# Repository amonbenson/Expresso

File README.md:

# Expresso

An open source USB&ndash;Midi&ndash;Expression pedal converter.

⚠️ Please note: This project is currently under heavy development and not yet functional. ⚠️

✔️ Supports sustain pedals of any polarity<br>
✔️ Supports any kind of three-pin analog expression pedal<br>
✔️ Pedal state can be output to both Din- or USB-Midi<br>
✔️ Can be used as a classic USB-Din-Midi adapter<br>

... to be continued.

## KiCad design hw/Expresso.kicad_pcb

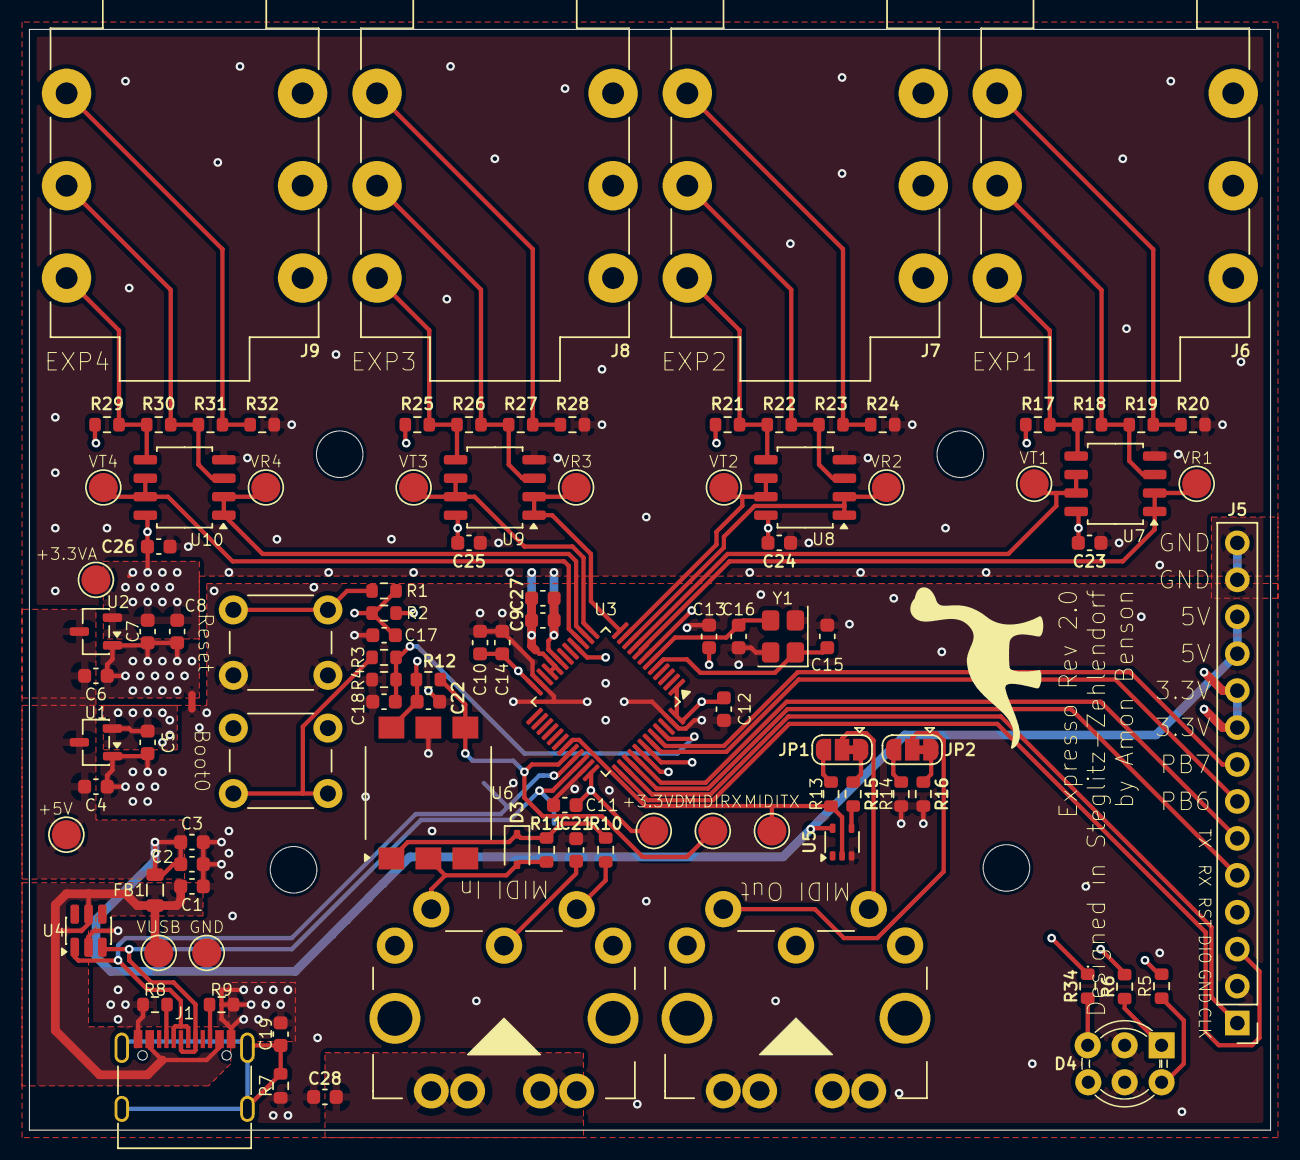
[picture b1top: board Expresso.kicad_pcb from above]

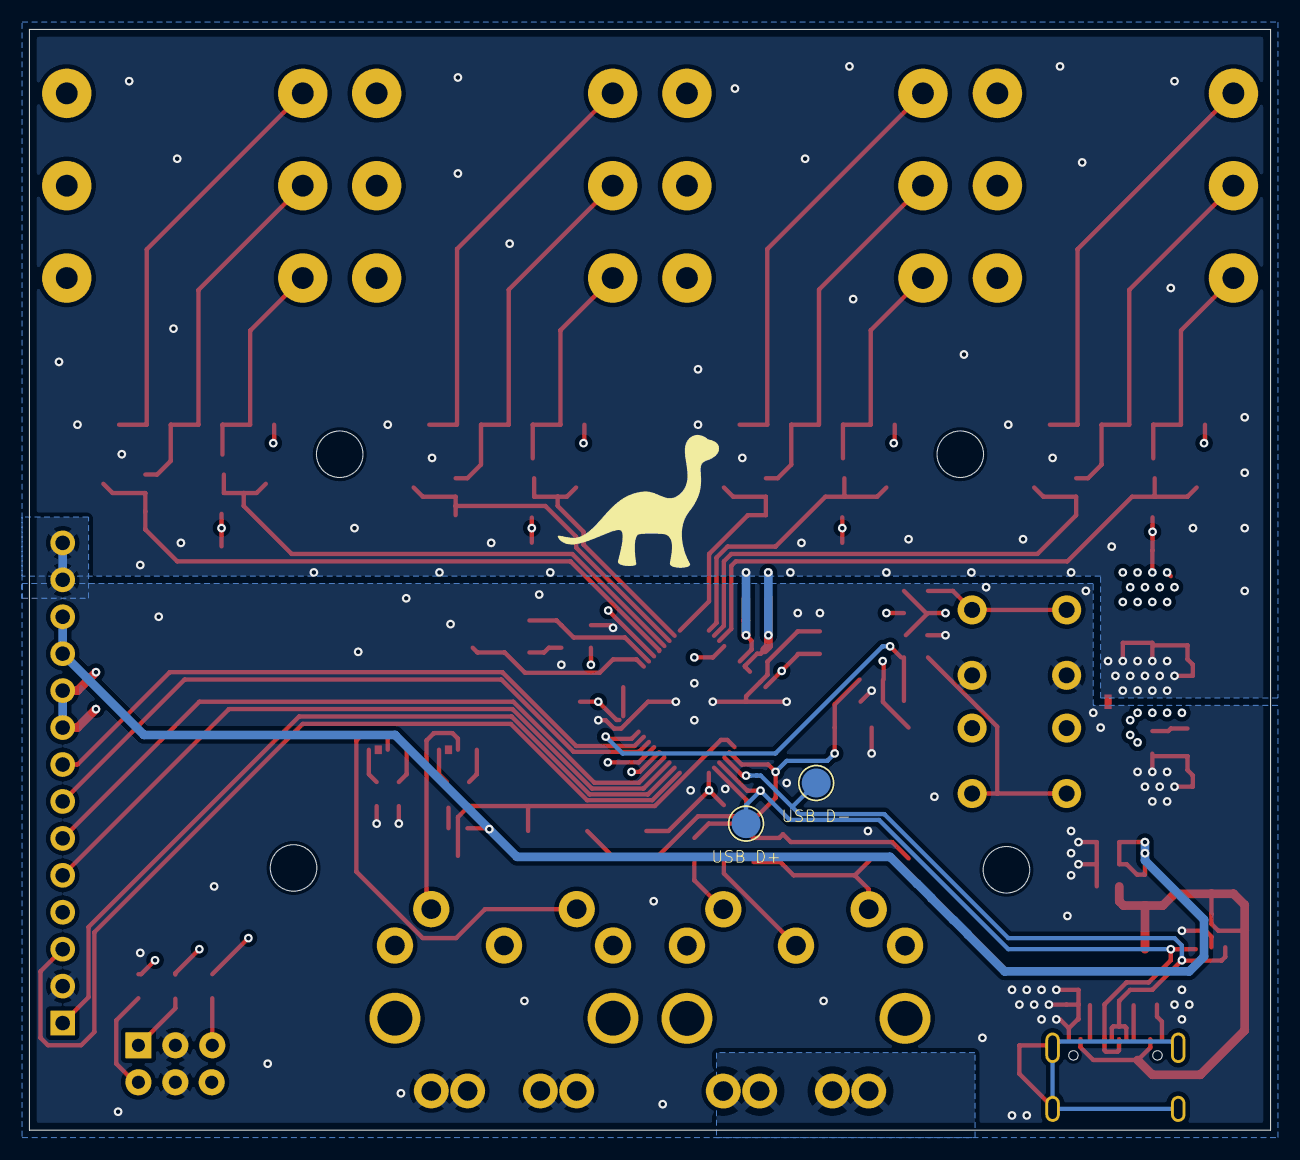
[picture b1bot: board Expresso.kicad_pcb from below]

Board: 4 copper layers, 85.3 x 75.7 mm, 108 parts (2 on the bottom side), 63 nets.

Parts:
C1: 10n; C_0603_1608Metric
C2, C8, C9, C11, C12, C13, C14, C17, C18, C21, C22, C23, C24, C25, C26, C28: 100n; C_0603_1608Metric
C3: 4.7u; C_0603_1608Metric
C4, C5, C6, C7, C27: 1u; C_0603_1608Metric
C10: 10u; C_0603_1608Metric
C15, C16: 12p; C_0603_1608Metric
C19: 4.7n; C_0603_1608Metric
D3: 1N4148WS; D_SOD-323
D4: LED_RBK_GBK; LED_D5.0mm_6Pin
FB1: 33Ω@100MHz; L_0805_2012Metric
H1, H2, H3, H4: MountingHole; MountingHole_3.2mm_M3
J1: USB_C_Receptacle_USB2.0_16P; USB_C_Receptacle_G-Switch_GT-USB-7010ASV
J2: Midi In; DIN5_MIDI_MultiGround
J3: Midi Out; DIN5_MIDI_MultiGround
J5: Debug; PinHeader_1x14_P2.54mm_Vertical
J6, J7, J8, J9: Exp; Jack_6.35mm_Neutrik_NMJ6HFD4_Horizontal
JP1: MidiOut_Src; SolderJumper-3_P1.3mm_Bridged12_RoundedPad1.0x1.5mm
JP2: MidiOut_Snk; SolderJumper-3_P1.3mm_Bridged12_RoundedPad1.0x1.5mm
NT1: GND_GNDA; NetTie-2_SMD_Pad0.5mm
R1, R3, R5, R11, R12: 1k; R_0603_1608Metric
R2, R4, R17, R20, R21, R24, R25, R28, R29, R32: 10k; R_0603_1608Metric
R6: 2.2k; R_0603_1608Metric
R7: 1M; R_0603_1608Metric
R8, R9: 5.1k; R_0603_1608Metric
R10, R15, R16: 220; R_0603_1608Metric
R13, R14: 47; R_0603_1608Metric
R18, R19, R22, R23, R26, R27, R30, R31: 100k; R_0603_1608Metric
R34: 680; R_0603_1608Metric
SW1: Reset; SW_PUSH_6mm
SW2: Boot0; SW_PUSH_6mm
TP1: VUSB; TestPoint_Pad_D2.0mm
TP2: +5V; TestPoint_Pad_D2.0mm
TP3: +3.3V; TestPoint_Pad_D2.0mm
TP4: +3.3VA; TestPoint_Pad_D2.0mm
TP5: GND; TestPoint_Pad_D2.0mm
TP6: USB D+; TestPoint_Pad_D2.0mm
TP7: USB D-; TestPoint_Pad_D2.0mm
TP8: MIDI_RX; TestPoint_Pad_D2.0mm
TP9: MIDI_TX; TestPoint_Pad_D2.0mm
TP10, TP12, TP14, TP16: VR; TestPoint_Pad_D2.0mm
TP11, TP13, TP15, TP17: VT; TestPoint_Pad_D2.0mm
U1, U2: XC6206P332MR; SOT-23-3
U3: STM32G431CBT6; LQFP-48_7x7mm_P0.5mm
U4: SRV05-4; SOT-23-6
U5: 74AHCT1G17GWH; SOT-353_SC-70-5
U6: H11L1; SOP-6_6.35x8.51mm_P02.54mm
U7, U8, U9, U10: NE5532; NE5532DR
Y1: 16 MHz; Crystal_SMD_3225-4Pin_3.2x2.5mm

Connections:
+3.3V: C5.1, C10.1, C11.1, C12.1, C13.1, C14.1, C22.1, J5.9, J5.10, R2.2, R12.1, SW2.2, TP3.1, U1.2 (VO), U3.1 (VBAT), U3.24 (VDD), U3.36 (VDD), U3.48 (VDD), U6.6
+3.3VA: C7.1, C8.1, C9.1, C23.1, C24.1, C25.1, C26.1, C27.1, R17.1, R21.1, R25.1, R29.1, TP4.1, U2.2 (VO), U3.20 (VREF+), U3.21 (VDDA), U7.8 (V+), U8.8 (V+), U9.8 (V+), U10.8 (V+)
+5V: C2.1, C3.1, C4.1, C6.1, FB1.2, J5.11, J5.12, TP2.1, U1.3 (VI), U2.3 (VI), U5.5 (VCC)
/Expression Inputs/Expression Input 1/EXP_R: J6.R, R18.2, R19.1, U7.3 (+)
/Expression Inputs/Expression Input 1/EXP_S: J6.S, R19.2, R20.1
/Expression Inputs/Expression Input 1/EXP_T: J6.T, R17.2, R18.1, U7.5 (+)
/Expression Inputs/Expression Input 2/EXP_R: J7.R, R22.2, R23.1, U8.3 (+)
/Expression Inputs/Expression Input 2/EXP_S: J7.S, R23.2, R24.1
/Expression Inputs/Expression Input 2/EXP_T: J7.T, R21.2, R22.1, U8.5 (+)
/Expression Inputs/Expression Input 3/EXP_R: J8.R, R26.2, R27.1, U9.3 (+)
/Expression Inputs/Expression Input 3/EXP_S: J8.S, R27.2, R28.1
/Expression Inputs/Expression Input 3/EXP_T: J8.T, R25.2, R26.1, U9.5 (+)
/Expression Inputs/Expression Input 4/EXP_R: J9.R, R30.2, R31.1, U10.3 (+)
/Expression Inputs/Expression Input 4/EXP_S: J9.S, R31.2, R32.1
/Expression Inputs/Expression Input 4/EXP_T: J9.T, R29.2, R30.1, U10.5 (+)
/Midi Connector/MIDI_IN_SHIELD: C28.1, J2.S
/USB Connector/USB_SHIELD: C19.1, J1.S1 (SHIELD), R7.1
GND: C1.2, C2.2, C3.2, C4.2, C5.2, C10.2, C11.2, C12.2, C13.2, C14.2, C15.2, C16.2, C17.2, C18.2, C19.2, C21.2, C22.2, C28.2, D4.2 (K1), D4.5 (K2), J1.A1 (GND), J1.A12 (GND), J1.B1 (GND), J1.B12 (GND), J3.S, J5.2, J5.13, J5.14, NT1.1, R4.1, R7.2, R8.2, R9.2, R14.1, R16.1, SW1.1, TP5.1, U1.1 (GND), U3.23 (VSS), U3.35 (VSS), U3.47 (VSS), U4.2 (VN), U5.3 (GND), U6.5, Y1.2, Y1.4
GNDA: C6.2, C7.2, C8.2, C9.2, C23.2, C24.2, C25.2, C26.2, C27.2, NT1.2, R20.2, R24.2, R28.2, R32.2, U2.1 (GND), U3.19 (VSSA), U7.4 (V-), U8.4 (V-), U9.4 (V-), U10.4 (V-)
unnamed: C21.1, J2.2
unnamed: D3.2 (A), J2.5, R11.2, U6.2
unnamed: D3.1 (K), R10.2, R11.1, U6.1
unnamed: D4.1 (B1A), R6.2
unnamed: D4.3 (GA), R34.2
unnamed: D4.6 (RA), R5.1
unnamed: J1.A5 (CC1), R8.1
unnamed: J1.B5 (CC2), R9.1
unnamed: J2.4, R10.1
unnamed: JP1.1 (A), R15.1
unnamed: JP1.3 (B), R13.2
unnamed: J3.4, JP1.2 (C)
unnamed: JP2.1 (A), R16.2
unnamed: JP2.3 (B), R14.2
unnamed: J3.5, JP2.2 (C)
unnamed: R1.1, SW1.2
unnamed: R3.1, SW2.1
unnamed: R15.2, U5.4
STM_ADC1_IN1: TP10.1, U3.8 (PA0), U7.1, U7.2 (-)
STM_ADC1_IN2: TP11.1, U3.9 (PA1), U7.6 (-), U7.7
STM_ADC1_IN3: TP12.1, U3.10 (PA2), U8.1, U8.2 (-)
STM_ADC1_IN4: TP13.1, U3.11 (PA3), U8.6 (-), U8.7
STM_ADC2_IN3: TP16.1, U3.14 (PA6), U10.1, U10.2 (-)
STM_ADC2_IN4: TP17.1, U3.15 (PA7), U10.6 (-), U10.7
STM_ADC2_IN13: TP15.1, U3.13 (PA5), U9.6 (-), U9.7
STM_ADC2_IN17: TP14.1, U3.12 (PA4), U9.1, U9.2 (-)
STM_BOOT0: C18.1, R3.2, R4.2, U3.45 (PB8)
STM_LED_B: R6.1, U3.42 (PB5)
STM_LED_G: R34.1, U3.16 (PB0)
STM_LED_R: R5.2, U3.41 (PB4)
STM_NRST: C17.1, J5.4, R1.2, R2.1, U3.7 (PG10)
STM_RCC_OSC_IN: C15.1, U3.5 (PF0), Y1.1
STM_RCC_OSC_OUT: C16.1, U3.6 (PF1), Y1.3
STM_SPARE1: J5.7, U3.43 (PB6)
STM_SPARE2: J5.8, U3.44 (PB7)
STM_SWCLK: J5.1, U3.38 (PA14)
STM_SWDIO: J5.3, U3.37 (PA13)
STM_USART1_RX: R12.2, TP8.1, U3.32 (PA10), U6.4
STM_USART1_TX: R13.1, TP9.1, U3.31 (PA9), U5.2
STM_USART2_RX: J5.5, U3.39 (PA15)
STM_USART2_TX: J5.6, U3.40 (PB3)
STM_USB_DM: J1.A7 (D-), J1.B7 (D-), TP7.1, U3.33 (PA11), U4.1 (IO1)
STM_USB_DP: J1.A6 (D+), J1.B6 (D+), TP6.1, U3.34 (PA12), U4.3 (IO2)
VUSB: C1.1, FB1.1, J1.A4 (VBUS), J1.A9 (VBUS), J1.B4 (VBUS), J1.B9 (VBUS), TP1.1, U4.5 (VP)

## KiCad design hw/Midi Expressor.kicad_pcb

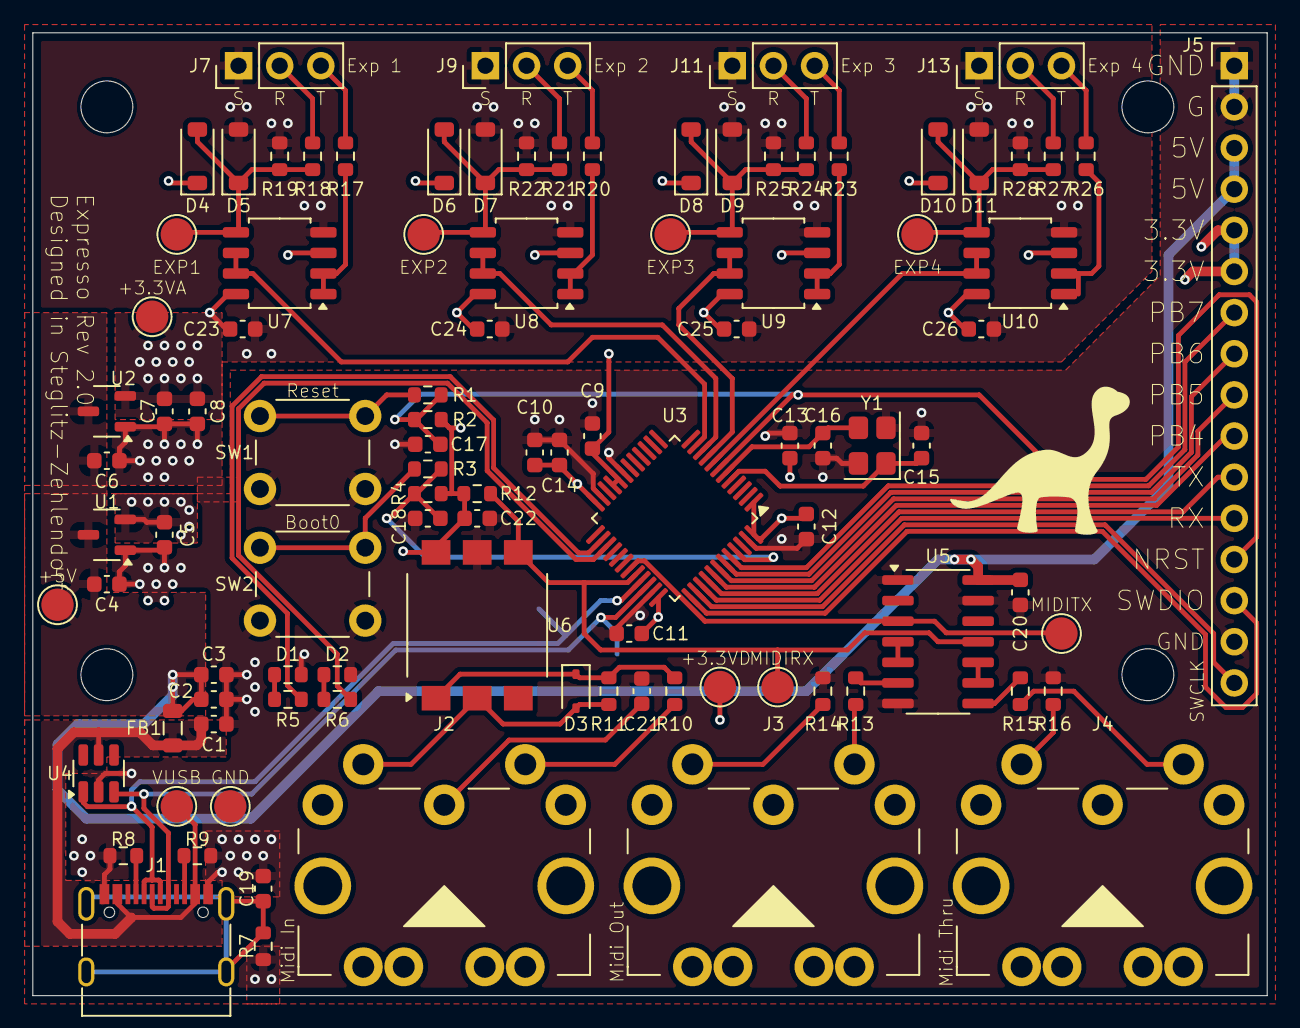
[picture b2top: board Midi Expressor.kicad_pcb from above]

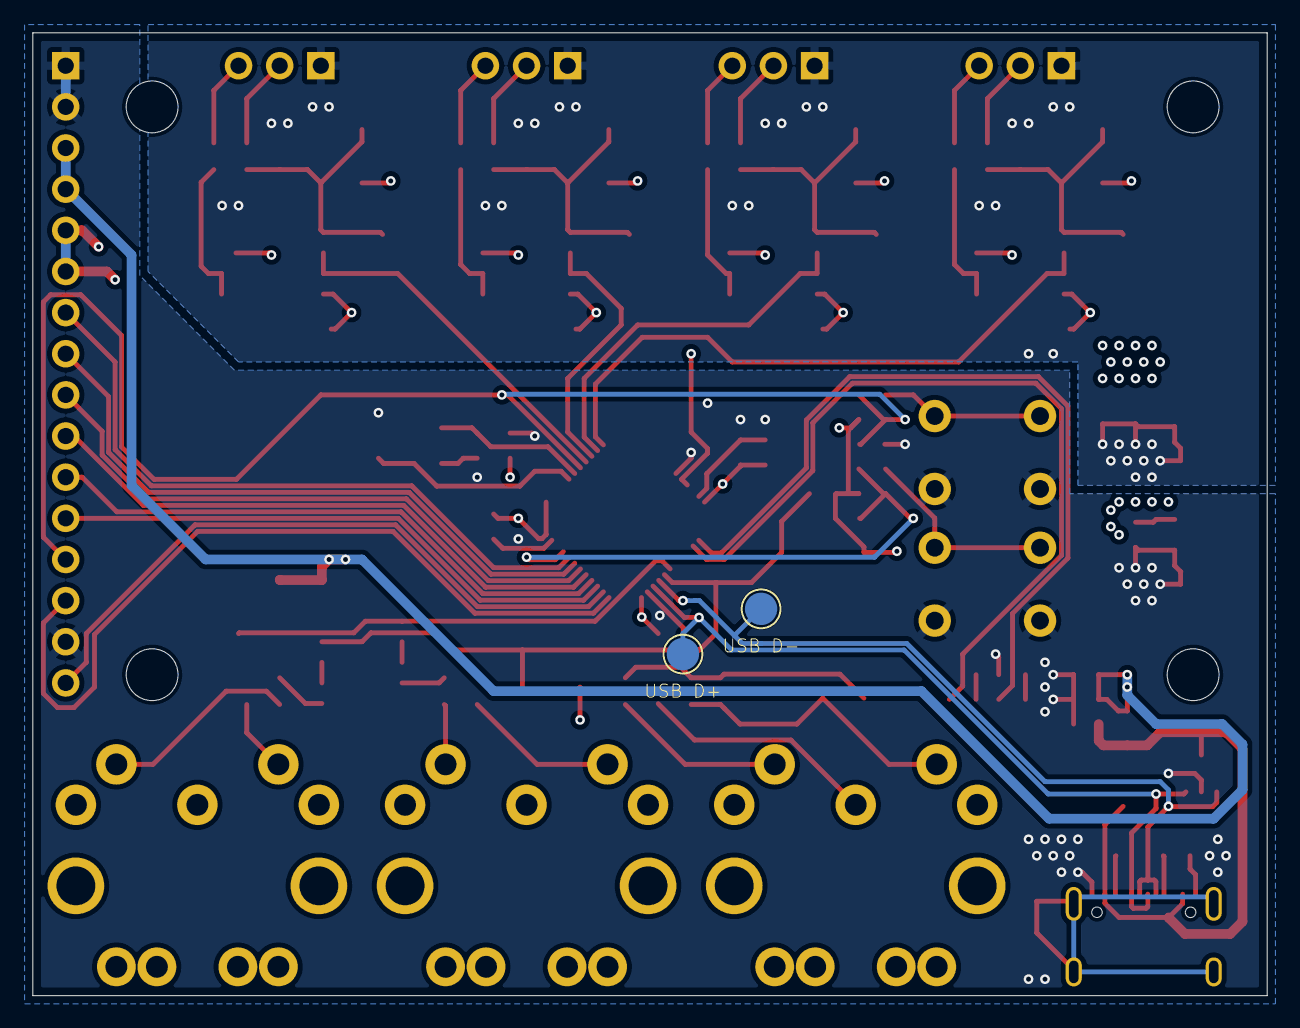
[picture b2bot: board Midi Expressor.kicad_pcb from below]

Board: 4 copper layers, 76.2 x 59.4 mm, 105 parts (2 on the bottom side), 62 nets.

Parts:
C1: 10n; C_0603_1608Metric
C2, C8, C9, C11, C12, C13, C14, C17, C18, C20, C21, C22, C23, C24, C25, C26: 100n; C_0603_1608Metric
C3: 4.7u; C_0603_1608Metric
C4, C5, C6, C7: 1u; C_0603_1608Metric
C10: 10u; C_0603_1608Metric
C15, C16: 12p; C_0603_1608Metric
C19: 4.7n; C_0603_1608Metric
D1, D2: Red; R_0603_1608Metric
D3: 1N4148WS; D_SOD-323
D4, D5, D6, D7, D8, D9, D10, D11: B5819W SL; D_SOD-123
FB1: 33Ω@100MHz; L_0805_2012Metric
H1, H2, H3, H4: MountingHole; MountingHole_3.2mm_M3
J1: USB_C_Receptacle_USB2.0_16P; USB_C_Receptacle_G-Switch_GT-USB-7010ASV
J2: Midi In; DIN5_MIDI_MultiGround
J3: Midi Out; DIN5_MIDI_MultiGround
J4: Midi Thru; DIN5_MIDI_MultiGround
J5: Debug; PinHeader_1x16_P2.54mm_Vertical
J7, J9, J11, J13: Exp Connector; PinHeader_1x03_P2.54mm_Vertical
R1, R3, R11, R12, R17, R18, R20, R21, R23, R24, R26, R27: 1k; R_0603_1608Metric
R2, R4: 10k; R_0603_1608Metric
R5, R6: 470; R_0603_1608Metric
R7: 1M; R_0603_1608Metric
R8, R9: 5.1k; R_0603_1608Metric
R10, R13, R14, R15, R16: 220; R_0603_1608Metric
R19, R22, R25, R28: 2M; R_0603_1608Metric
SW1: Reset; SW_PUSH_6mm
SW2: Boot0; SW_PUSH_6mm
TP1: VUSB; TestPoint_Pad_D2.0mm
TP2: +5V; TestPoint_Pad_D2.0mm
TP3: +3.3V; TestPoint_Pad_D2.0mm
TP4: +3.3VA; TestPoint_Pad_D2.0mm
TP5: GND; TestPoint_Pad_D2.0mm
TP6: MIDI_RX; TestPoint_Pad_D2.0mm
TP7: MIDI_TX; TestPoint_Pad_D2.0mm
TP8, TP9, TP10, TP11: EXP; TestPoint_Pad_D2.0mm
TP12: USB D-; TestPoint_Pad_D2.0mm
TP13: USB D+; TestPoint_Pad_D2.0mm
U1, U2: XC6206P332MR; SOT-23-3
U3: STM32G431CBT6; LQFP-48_7x7mm_P0.5mm
U4: SRV05-4; SOT-23-6
U5: 74HC14; SOIC-14_3.9x8.7mm_P1.27mm
U6: H11L1; SOP-6_6.35x8.51mm_P02.54mm
U7, U8, U9, U10: NE5532; NE5532DR
Y1: 16 MHz; Crystal_SMD_3225-4Pin_3.2x2.5mm

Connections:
+3.3V: C5.1, C10.1, C11.1, C12.1, C13.1, C14.1, C22.1, J5.5, J5.6, R2.2, R4.2, R12.1, TP3.1, U1.2 (VO), U3.1 (VBAT), U3.24 (VDD), U3.36 (VDD), U3.48 (VDD), U6.6
+3.3VA: C7.1, C8.1, C9.1, C23.1, C24.1, C25.1, C26.1, D4.1 (K), D6.1 (K), D8.1 (K), D10.1 (K), TP4.1, U2.2 (VO), U3.20 (VREF+), U3.21 (VDDA), U7.3 (+), U7.8 (V+), U8.3 (+), U8.8 (V+), U9.3 (+), U9.8 (V+), U10.3 (+), U10.8 (V+)
+5V: C2.1, C3.1, C4.1, C6.1, C20.1, FB1.2, J5.3, J5.4, TP2.1, U1.3 (VI), U2.3 (VI), U5.14 (VCC)
/Expression Inputs/Expression Input 1/EXP_REF: R17.2, U7.1, U7.2 (-)
/Expression Inputs/Expression Input 1/EXP_SENSE: D4.2 (A), D5.1 (K), R18.2, R19.1, TP8.1, U7.5 (+)
/Expression Inputs/Expression Input 2/EXP_REF: R20.2, U8.1, U8.2 (-)
/Expression Inputs/Expression Input 2/EXP_SENSE: D6.2 (A), D7.1 (K), R21.2, R22.1, TP9.1, U8.5 (+)
/Expression Inputs/Expression Input 3/EXP_REF: R23.2, U9.1, U9.2 (-)
/Expression Inputs/Expression Input 3/EXP_SENSE: D8.2 (A), D9.1 (K), R24.2, R25.1, TP10.1, U9.5 (+)
/Expression Inputs/Expression Input 4/EXP_REF: R26.2, U10.1, U10.2 (-)
/Expression Inputs/Expression Input 4/EXP_SENSE: D10.2 (A), D11.1 (K), R27.2, R28.1, TP11.1, U10.5 (+)
/USB Connector/USB_SHIELD: C19.1, J1.S1 (SHIELD), R7.1
GND: C1.2, C2.2, C3.2, C4.2, C5.2, C6.2, C7.2, C8.2, C9.2, C10.2, C11.2, C12.2, C13.2, C14.2, C15.2, C16.2, C17.2, C18.2, C19.2, C20.2, C21.2, C22.2, C23.2, C24.2, C25.2, C26.2, D1.1 (K), D2.1 (K), D5.2 (A), D7.2 (A), D9.2 (A), D11.2 (A), J1.A1 (GND), J1.A12 (GND), J1.B1 (GND), J1.B12 (GND), J5.1, J5.2, J5.15, J7.1, J9.1, J11.1, J13.1, R7.2, R8.2, R9.2, R14.2, R16.2, R19.2, R22.2, R25.2, R28.2, SW1.1, SW2.1, TP5.1, U1.1 (GND), U2.1 (GND), U3.19 (VSSA), U3.23 (VSS), U3.35 (VSS), U3.47 (VSS), U4.2 (VN), U5.1, U5.7 (GND), U5.13, U6.5, U7.4 (V-), U8.4 (V-), U9.4 (V-), U10.4 (V-), Y1.2, Y1.4
unnamed: C21.1, J2.2
unnamed: D1.2 (A), R5.2
unnamed: D2.2 (A), R6.2
unnamed: D3.2 (A), J2.5, R11.2, U6.2
unnamed: D3.1 (K), R10.2, R11.1, U6.1
unnamed: J1.A5 (CC1), R8.1
unnamed: J1.B5 (CC2), R9.1
unnamed: J2.4, R10.1
unnamed: J3.4, R13.1
unnamed: J3.5, R14.1
unnamed: J4.4, R15.1
unnamed: J4.5, R16.1
unnamed: J7.2, R18.1
unnamed: J7.3, R17.1
unnamed: J9.2, R21.1
unnamed: J9.3, R20.1
unnamed: J11.2, R24.1
unnamed: J11.3, R23.1
unnamed: J13.2, R27.1
unnamed: J13.3, R26.1
unnamed: R1.1, SW1.2
unnamed: R3.1, SW2.2
unnamed: R13.2, U5.6
unnamed: R15.2, U5.8
unnamed: U5.4, U5.5
unnamed: U5.9, U5.10
STM_ADC1_IN1: U3.8 (PA0), U10.6 (-), U10.7
STM_ADC1_IN2: U3.9 (PA1), U9.6 (-), U9.7
STM_ADC1_IN3: U3.10 (PA2), U8.6 (-), U8.7
STM_ADC1_IN4: U3.11 (PA3), U7.6 (-), U7.7
STM_BOOT0: C18.1, R3.2, R4.1, U3.45 (PB8)
STM_LED1: R5.1, U3.26 (PB12)
STM_LED2: R6.1, U3.27 (PB13)
STM_NRST: C17.1, J5.13, R1.2, R2.1, U3.7 (PG10)
STM_RCC_OSC_IN: C15.1, U3.5 (PF0), Y1.1
STM_RCC_OSC_OUT: C16.1, U3.6 (PF1), Y1.3
STM_SPARE1: J5.10, U3.41 (PB4)
STM_SPARE2: J5.9, U3.42 (PB5)
STM_SPARE3: J5.8, U3.43 (PB6)
STM_SPARE4: J5.7, U3.44 (PB7)
STM_SWCLK: J5.16, U3.38 (PA14)
STM_SWDIO: J5.14, U3.37 (PA13)
STM_USART1_RX: R12.2, TP6.1, U3.32 (PA10), U5.11, U6.4
STM_USART1_TX: TP7.1, U3.31 (PA9), U5.3
STM_USART2_RX: J5.12, U3.39 (PA15)
STM_USART2_TX: J5.11, U3.40 (PB3)
STM_USB_DM: J1.A7 (D-), J1.B7 (D-), TP12.1, U3.33 (PA11), U4.1 (IO1)
STM_USB_DP: J1.A6 (D+), J1.B6 (D+), TP13.1, U3.34 (PA12), U4.3 (IO2)
VUSB: C1.1, FB1.1, J1.A4 (VBUS), J1.A9 (VBUS), J1.B4 (VBUS), J1.B9 (VBUS), TP1.1, U4.5 (VP)

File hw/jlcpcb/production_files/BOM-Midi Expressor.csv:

Comment,Designator,Footprint,LCSC,Quantity
100n,"C11,C12,C13,C14,C17,C18,C2,C20,C21,C22,C23,C24,C25,C26,C8,C9",C_0603_1608Metric,C14663,16
10k,"R2,R4",R_0603_1608Metric,C25804,2
10n,C1,C_0603_1608Metric,C57112,1
10u,C10,C_0603_1608Metric,C19702,1
12p,"C15,C16",C_0603_1608Metric,C38523,2
16 MHz,Y1,Crystal_SMD_3225-4Pin_3.2x2.5mm,C13738,1
1M,R7,R_0603_1608Metric,C22935,1
1N4148WS,D3,D_SOD-323,C2128,1
1k,"R1,R11,R12,R17,R18,R20,R21,R23,R24,R26,R27,R3",R_0603_1608Metric,C21190,12
1u,"C4,C5,C6,C7",C_0603_1608Metric,C15849,4
220,"R10,R13,R14,R15,R16",R_0603_1608Metric,C22962,5
2M,"R19,R22,R25,R28",R_0603_1608Metric,C22976,4
33Ω@100MHz,FB1,L_0805_2012Metric,C1015,1
4.7n,C19,C_0603_1608Metric,C53987,1
4.7u,C3,C_0603_1608Metric,C19666,1
470,"R5,R6",R_0603_1608Metric,C23179,2
5.1k,"R8,R9",R_0603_1608Metric,C23186,2
74HC14,U5,SOIC-14_3.9x8.7mm_P1.27mm,C5605,1
B5819W SL,"D10,D11,D4,D5,D6,D7,D8,D9",D_SOD-123,C8598,8
H11L1,U6,SOP-6_6.35x8.51mm_P02.54mm,C899473,1
NE5532,"U10,U7,U8,U9",SOIC-8_5.3x5.3mm_P1.27mm,C7426,4
Red,"D1,D2",R_0603_1608Metric,C2286,2
SRV05-4,U4,SOT-23-6,C85364,1
STM32G431CBT6,U3,LQFP-48_7x7mm_P0.5mm,C529355,1
USB_C_Receptacle_USB2.0_16P,J1,USB_C_Receptacle_G-Switch_GT-USB-7010ASV,C393939,1
XC6206P332MR,"U1,U2",SOT-23-3,C5446,2

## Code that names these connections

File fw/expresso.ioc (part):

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Mcu.Name=STM32G431C(6-8-B)Tx
Mcu.Package=LQFP48
Mcu.UserName=STM32G431CBTx
PA0.Mode=IN1-Single-Ended
PA0.Signal=ADC1_IN1
PA1.Mode=IN2-Single-Ended
PA1.Signal=ADC1_IN2
PA10.Mode=Asynchronous
PA10.Signal=USART1_RX
PA11.Mode=Device
PA11.Signal=USB_DM
PA12.Mode=Device
PA12.Signal=USB_DP
PA13.Mode=Serial_Wire
PA13.Signal=SYS_JTMS-SWDIO
PA14.Mode=Serial_Wire
PA14.Signal=SYS_JTCK-SWCLK
PA15.Mode=Asynchronous
PA15.Signal=USART2_RX
PA2.Mode=IN3-Single-Ended
PA2.Signal=ADC1_IN3
PA3.Mode=IN4-Single-Ended
PA3.Signal=ADC1_IN4
PA4.Mode=IN17-Single-Ended
PA4.Signal=ADC2_IN17
PA5.Mode=IN13-Single-Ended
PA5.Signal=ADC2_IN13
PA6.Mode=IN3-Single-Ended
PA6.Signal=ADC2_IN3
PA7.Mode=IN4-Single-Ended
PA7.Signal=ADC2_IN4
PA9.Mode=Asynchronous
PA9.Signal=USART1_TX
PB0.GPIOParameters=GPIO_Label
PB0.GPIO_Label=LED_B
PB0.Signal=S_TIM3_CH3
PB3.Mode=Asynchronous
PB3.Signal=USART2_TX
PB4.GPIOParameters=GPIO_Label
PB4.GPIO_Label=LED_R
PB4.Signal=S_TIM3_CH1
PB5.GPIOParameters=GPIO_Label
PB5.GPIO_Label=LED_G
PB5.Signal=S_TIM3_CH2
PB6.GPIOParameters=GPIO_Label
PB6.GPIO_Label=GPIO_SPARE1
PB6.Signal=GPIO_Input
PB7.GPIOParameters=GPIO_Label
PB7.GPIO_Label=GPIO_SPARE2
PB7.Signal=GPIO_Input
PF0-OSC_IN.Mode=HSE-External-Oscillator
PF0-OSC_IN.Signal=RCC_OSC_IN
PF1-OSC_OUT.Mode=HSE-External-Oscillator
PF1-OSC_OUT.Signal=RCC_OSC_OUT
RCC.HSE_VALUE=16000000
RCC.SYSCLKFreq_VALUE=16000000
board=custom

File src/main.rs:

#![no_std]
#![no_main]

use core::sync::atomic::{AtomicBool, Ordering};

use defmt::*;
use embassy_executor::Spawner;
use embassy_futures::join::join;
use embassy_stm32::gpio::{AnyPin, Level, Output, Speed};
use embassy_stm32::usb::Driver;
use embassy_stm32::{Config, bind_interrupts, peripherals, usb};
use embassy_stm32::adc::{Adc, AdcChannel, AdcConfig, AnyAdcChannel, Resolution, SampleTime};
use embassy_sync::blocking_mutex::raw::ThreadModeRawMutex;
use embassy_sync::channel::Channel;
use embassy_usb::class::midi::MidiClass;
use embassy_usb::driver::EndpointError;
use embassy_usb::{Builder, Handler};
use embassy_usb::control::OutResponse;
use midi_types::MidiMessage;
use midi_types::status::CONTROL_CHANGE;
use usbd_hid::descriptor::{KeyboardReport, SerializedDescriptor};
use crate::channel_strip::ChannelStrip;

use {defmt_rtt as _, panic_probe as _};

mod channel_strip;

const NUM_CHANNELS: usize = 4;

bind_interrupts!(struct Irqs {
    USB_LP => usb::InterruptHandler<peripherals::USB>;
});

#[embassy_executor::main]
async fn main(_spawner: Spawner) {
    let config = Config::default();
    let p = embassy_stm32::init(config);

    info!("Initializing LED outputs...");
    let mut led1 = Output::new(p.PB12, Level::Low, Speed::Low);
    let mut led2 = Output::new(p.PB13, Level::Low, Speed::Low);

    info!("Initializing ADC...");
    let config = AdcConfig {
        resolution: Some(Resolution::BITS12),
        ..AdcConfig::default()
    };
    let mut adc = Adc::new(p.ADC1, config);
    let mut adc_channels = [
        p.PA0.degrade_adc(),
        p.PA1.degrade_adc(),
        p.PA2.degrade_adc(),
        p.PA3.degrade_adc(),
    ];

    info!("Initializing USB");
    let driver = Driver::new(
        p.USB,
        Irqs,
        p.PA12,
        p.PA11,
    );

    let mut config = embassy_usb::Config::new(0x1209, 0xd2b3);
    config.manufacturer = Some("schlegelflegel");
    config.product = Some("Midi Expressor");
    config.serial_number = Some("0.3.0");
    config.max_power = 100;
    config.max_packet_size_0 = 64;

    // Required for windows compatibility.
    // https://developer.nordicsemi.com/nRF_Connect_SDK/doc/1.9.1/kconfig/CONFIG_CDC_ACM_IAD.html#help
    config.device_class = 0xEF;
    config.device_sub_class = 0x02;
    config.device_protocol = 0x01;
    config.composite_with_iads = true;

    // Create embassy-usb DeviceBuilder using the driver and config.
    // It needs some buffers for building the descriptors.
    let mut config_descriptor = [0; 256];
    let mut bos_descriptor = [0; 256];
    let mut control_buf = [0; 64];

    let mut builder = Builder::new(
        driver,
        config,
        &mut config_descriptor,
        &mut bos_descriptor,
        &mut [], // no msos descriptors
        &mut control_buf,
    );
    let mut midi_class = MidiClass::new(&mut builder, 1, 1, 64);
    let mut usb = builder.build();

    let mut channel_strips = [ChannelStrip::default(); NUM_CHANNELS];

    let mut usb_fut = usb.run();

    let mut midi_fut = async {
        loop {
            midi_class.wait_connection().await;
            info!("USB Connected");
            let _ = midi_session(&mut midi_class).await;
            info!("USB Disconnected");
        }
    };

    // let in_fut = async {
    //     loop {
    //         for (i, channel_strip) in channel_strips.iter_mut().enumerate() {
    //             let raw_value = adc.blocking_read(&mut adc_channels[i], SampleTime::CYCLES24_5);

    //             channel_strip.process(raw_value);

    //             if channel_strip.changed() {
    //                 info!("Channel {}: Value = {}", i, channel_strip.value())
    //             }
    //         }
    //     }
    // };

    join(usb_fut, midi_fut).await;
}

pub struct Disconnected;

impl From<EndpointError> for Disconnected {
    fn from(value: EndpointError) -> Self {
        match value {
            EndpointError::BufferOverflow => defmt::panic!("Buffer overflow"),
            EndpointError::Disabled => Disconnected,
        }
    }
}

static MIDI_QUEUE: Channel<ThreadModeRawMutex, MidiMessage, 10> = Channel::new();

pub async fn midi_session<'d, T: usb::Instance + 'd>(midi: &mut MidiClass<'d, Driver<'d, T>>) -> Result<(), Disconnected> {
    loop {
        let msg = MIDI_QUEUE.receive().await;
        match msg {
            MidiMessage::ControlChange(channel, control, value) => {
                let cin = CONTROL_CHANGE >> 4;
                let status = CONTROL_CHANGE << 4 | u8::from(channel);
                let packet = [CONTROL_CHANGE >> 4, status, u8::from(control), u8::from(value)];
                midi.write_packet(&packet).await?;
            }
            _ => {}
        }
    }
}

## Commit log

2026-01-11 rework channel_strip to update with a single message
2026-01-11 added with methods
2026-01-11 added labels and some minor layout changes
2026-01-11 UI cleanup
2026-01-11 ui layout changes, added knob placeholders
2026-01-11 removed knob for now
2026-01-11 updated labels
2026-01-13 more midi class updates
2026-01-13 moved files to firmware directory
2026-01-13 moved files to software directory
2026-01-13 added hardware directory and main workspace files
2026-01-13 merged cargo directories into one workspace and added correct build commands
2026-01-13 Add MIT License to the project
2026-01-13 Add initial README with work in progress note
2026-01-13 updated theming variables
2026-01-13 theme updates
2026-01-13 removed unused imports
2026-01-13 added message and some basic test
2026-01-14 updated hardware issues for PBC revision 2
2026-02-25 added tauri initial project
2026-03-03 huge schematic rework
2026-03-03 added MacOS stuff to gitignore
2026-03-03 added new pcb design, ERC errors not fixed yet
2026-03-03 saved kicad project
2026-03-04 small PCB updates for casing design
2026-03-04 added new flash commands
2026-03-04 udpated toolchain and ide settings
2026-03-04 added cubemx file
2026-03-04 removed unused ADC pin
2026-03-04 modified firmware
2026-03-04 updates to hardware layer
2026-03-04 added basic adc example
2026-03-04 updated midi device layout
2026-03-04 more progress, though not working atm.
2026-03-05 added working USB class descriptor
2026-03-05 USB midi working
2026-03-05 added din midi
2026-03-05 ran rust formatter
2026-03-05 updated midi circuit to use 3.3V logic level
2026-03-05 added resistance calculation formulas
2026-03-05 initial core structure
2026-03-05 fixed issues with the algorithm
2026-03-05 restructured midi encoders/decoders into multiple files
2026-03-05 more restructuring of core components
2026-03-05 added channel tests
2026-03-06 added complete channel group
2026-03-06 added snafu error checking
2026-03-06 added channel group tests
2026-03-06 added router components
2026-03-07 added usb/din midi connectors and specific tests
2026-03-07 updated firmware implementation, untested
2026-03-07 added new firmware workings
2026-03-07 core restructure builds nicely!
2026-03-07 added compatibility mode for the default expression pedal behavior
2026-03-07 added temporary fallback uart output pin
2026-03-07 added global settings
2026-03-07 fixed import ordering
2026-03-07 added example sysex handler
2026-03-07 refactored sysex and MidiMessage struct
2026-03-07 updated firmware version
2026-03-07 added crude sysex settings serializer
2026-03-08 replaced const generic by a global constant
2026-03-08 replaced component with two seperate midi traits
2026-03-08 fixed sysex tests
2026-03-08 updates to sysex handling
2026-03-08 added sysex patch command
2026-03-08 Added full frontend app.
2026-03-08 added full sysex message handeling on frontend
2026-03-10 removed MIDI Thru and updated Connector positioning
2026-03-11 updated PCB thickness, added 3d model file
2026-03-11 updated connector positions and added new RGB led
2026-03-12 updated front panel designs
2026-03-12 more updates to front panel
2026-03-12 refactored software code into main library
2026-03-12 added status led in firmware, currently untested
2026-03-12 added new LED traces to hardware
2026-03-13 added customizable settings
2026-03-13 updated global cargo tasks
2026-03-13 added argument parser to xtask
2026-03-13 added github ci
2026-03-13 added missing library
2026-03-13 updated checkout version for software test
2026-03-13 added github release workflow
2026-03-13 added status badge
2026-03-13 merged package versions and updated release CI
2026-03-13 merged package versions and updated release CI with correct filenames
2026-03-13 added sysex handling to status updates and changed xtasks
2026-03-13 fixed firmware boot issue
2026-03-15 updated status event push messages
2026-03-15 updated initial renode test files to make them compile
2026-03-15 added renode tests to xtask
2026-03-15 updated renode CI
2026-03-15 fixed renode version in CI
2026-03-15 fixed requirements install
2026-03-15 udpated test-fw to work cross-platform
2026-03-15 fixed ci command
2026-03-15 more path updates
2026-03-15 switched to pre-built renode image
2026-03-15 forced CI to use node v24
2026-03-15 remove firmware check (replaced by full test)
2026-03-16 fixed a bug where a running status message would be modified
2026-03-16 added code coverage
2026-03-16 fixed library name in coverage test
2026-03-16 fixed unsupported embassy feature in CI coverage
2026-03-16 added coverage report xml as artifact
2026-03-17 added final production files for version 2
2026-04-07 added minimum input delta
2026-04-07 changed defaults
2026-04-07 fixed input range issue
2026-04-07 udpated minimum delta
2026-04-07 fixed firmware tests
2026-04-07 added flash storage
2026-04-08 updates to readme
2026-04-08 added more tests
2026-04-08 added test explorer pane
2026-04-08 added release job
2026-04-08 stripped old feature flags, coverage improvements
2026-04-08 fixed invalid cargo path in vscode settings
2026-04-08 updated release task
2026-04-08 removed manual release target
